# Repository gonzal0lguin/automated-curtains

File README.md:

# automated-curtains

Motorized roller blinds controlled by an ESP32: a NEMA 17 stepper with a
TMC2209 driver, an AS5600 magnetic encoder for absolute position, and a
smart-knob style controller (rotary encoder and GC9A01 round display). It also
has a web app and API, so an iPhone Shortcut can open the blinds when the alarm
goes off.

- Project idea and goals: [idea.md](idea.md)
- Firmware, wiring, setup, API and testing: [firmware/README.md](firmware/README.md)

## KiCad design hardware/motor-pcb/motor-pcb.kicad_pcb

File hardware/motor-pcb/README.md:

# Smart Blinds — motor encoder board

KiCad 10 project for the small board that sits on the back of the NEMA 17
stepper. It carries the AS5600 magnetic encoder on the shaft axis and the
RJ45 that links the motor to the control panel
([`../blinds-pcb`](../blinds-pcb/README.md)).

**Status: rev A, first layout** (2026-11-17). Schematic ERC clean
([`doc/schematic.pdf`](doc/schematic.pdf)); PCB placed, routed, DRC clean
(0 violations, 0 unconnected, schematic parity clean); fabrication files in
[`fab/`](fab/).

| Outer face | Motor side |
|---|---|
|  |  |

(The motor-side render is seen from below, so it is mirrored.)

## What is on the board

| Ref | Part | Side | Why |
|---|---|---|---|
| U1 | AS5600-ASOM, SOIC-8 | motor | 12-bit angle of the magnet on the shaft, I2C address 0x36 |
| C1, C2 | 100 nF + 1 µF | motor | AS5600 supply (3.3 V operation: VDD5V and VDD3V3 tied together, as in the datasheet) |
| JP1 | 3-pad solder jumper | motor | AS5600 DIR pin. Default bridged to GND (CW); cut and bridge 2–3 for CCW |
| J1 | RJ45 Amphenol 54602-908LF, no magnetics | outer | Cable to the panel. Same jack and pinout as panel J2 |
| J2 | JST-XH 4-pin, vertical | outer | Motor cable: 1 A1, 2 A2 (coil A), 3 B1, 4 B2 (coil B) |
| R1, R2 | 4.7k | outer | I2C pull-ups at the far end; with the panel's 10k ≈ 3.2k total |
| D2 | PESD3V3L2BT | outer | ESD clamp on SDA / SCL where the cable enters |
| C3 | 10 µF | outer | 3V3 bulk at the cable entry |
| R3, D1 | 1k + green LED | outer | Lights when the cable brings 3V3 (≈1 mA) |
| TP1–TP3 | test pads | outer | 3V3, GND, AS5600 OUT (analog angle). SDA / SCL: probe R1 / R2 |
| H1–H4 | M3, non-plated | — | 31 mm NEMA 17 hole pattern |

RJ45 pinout (straight T568B cable, identical to the panel):

| Pin | 1 | 2 | 3 | 4 | 5 | 6 | 7 | 8 |
|---|---|---|---|---|---|---|---|---|
| Signal | Coil A1 | Coil A2 | Coil B1 | SDA | GND | Coil B2 | SCL | 3V3 |

**Not Ethernet.** Never plug it into a network device, and never unplug it
while the panel is powered (motor coils).

## Mechanics

- Board 42.3 × 42.3 mm (the motor body), corners r 3, 1.6 mm FR-4.
- Mounted with four long M3 screws through the motor's own holes (31 mm
  pattern) and spacers. Copper is kept 3.6 mm from each hole for washers
  and spacers; the holes are not plated and not connected to GND (the motor
  case stays floating).
- U1 is exactly on the board centre = shaft axis, on the side facing the
  motor. Needs a **dual-shaft motor** (or a magnet holder on the rear shaft).
- Magnet: diametrically magnetised, Ø6 × 2.5 mm (Ø8 × 3 also works), glued
  centred on the shaft end. Air gap magnet face → chip top **0.5–3 mm**
  (chip is 1.5 mm tall). Choose the spacer length for this.
- Only U1, C1, C2, JP1 are on the motor side. **Trim the RJ45 and XH leads
  flush** after soldering (they come through on the motor side).
- Coil tracks are 0.8 mm (0.6 mm for B2), routed as pairs along the left and
  bottom edges, at least 7 mm from U1. At 1 A they make well under 1 mT at
  the chip, against the magnet's 30–90 mT, and the AS5600 rejects uniform
  stray fields.

## Firmware notes

- Same bus as before: AS5600 at 0x36 on GPIO21/22; keep `I2C_FREQ_HZ 100000`
  (see `../blinds-pcb/doc/pinmap.md`).
- JP1 default (DIR = GND): the angle rises clockwise **seen from the chip
  top**, i.e. from the motor towards the board. If the closed loop counts the
  wrong way, flip it in firmware or re-bridge JP1 — do not swap coil wires.
- AS5600 OUT on TP3 gives an analog angle (0–3.3 V) for a quick magnet check
  with a multimeter while turning the shaft by hand.

## Ordering

`fab/motor-pcb-gerbers.zip` (gerbers + drills), `fab/motor-pcb-pos.csv`,
`fab/lcsc-order.csv`. 2 layers, 1.6 mm, any colour; JLCPCB minimums are met
(0.25 mm tracks, 0.3 mm vias, 0.15 mm silk lines, 0.8 mm text).

**AS5600 stock:** LCSC C79815 showed only 7 pieces on 2026-11-17; buy it at
Mouser / Digi-Key if needed. Do **not** substitute the AS5600L: same package,
but I2C address 0x40 (the firmware expects 0x36).

## Files and scripts

| File | Contents |
|---|---|
| `tools/gen_schematic.py` | Writes `motor-pcb.kicad_sch` and checks the netlist (uses `../blinds-pcb/tools/gen_schematic/sch.py`) |
| `tools/build_pcb.py` | Rebuilds the whole board from the schematic: footprints, outline, holes, placement, routing, GND zones |
| `tools/silk.py` | Silkscreen: references, labels, flag, emblem |
| `tools/artwork.py` | Flag drawing and emblem helpers, shared by `silk.py` and `export_svg.py` (no KiCad needed) |
| `tools/export_svg.py` | Writes the logos as SVG to [`../artwork/`](../artwork/README.md) (with and without text / hatching) |
| `tools/emblem_small.py` | Small "ANDES MADE" volcano emblem (reuses the panel's `emblem.py`), writes `tools/emblem_small.json` |
| `lib/motor.kicad_sym` | AS5600 symbol (KiCad has none) |

Script order, KiCad closed: `gen_schematic.py` → `build_pcb.py` → `silk.py`,
then DRC. **Every script overwrites its output**, including edits made by hand
in KiCad; once the board is edited by hand, stop re-running them.

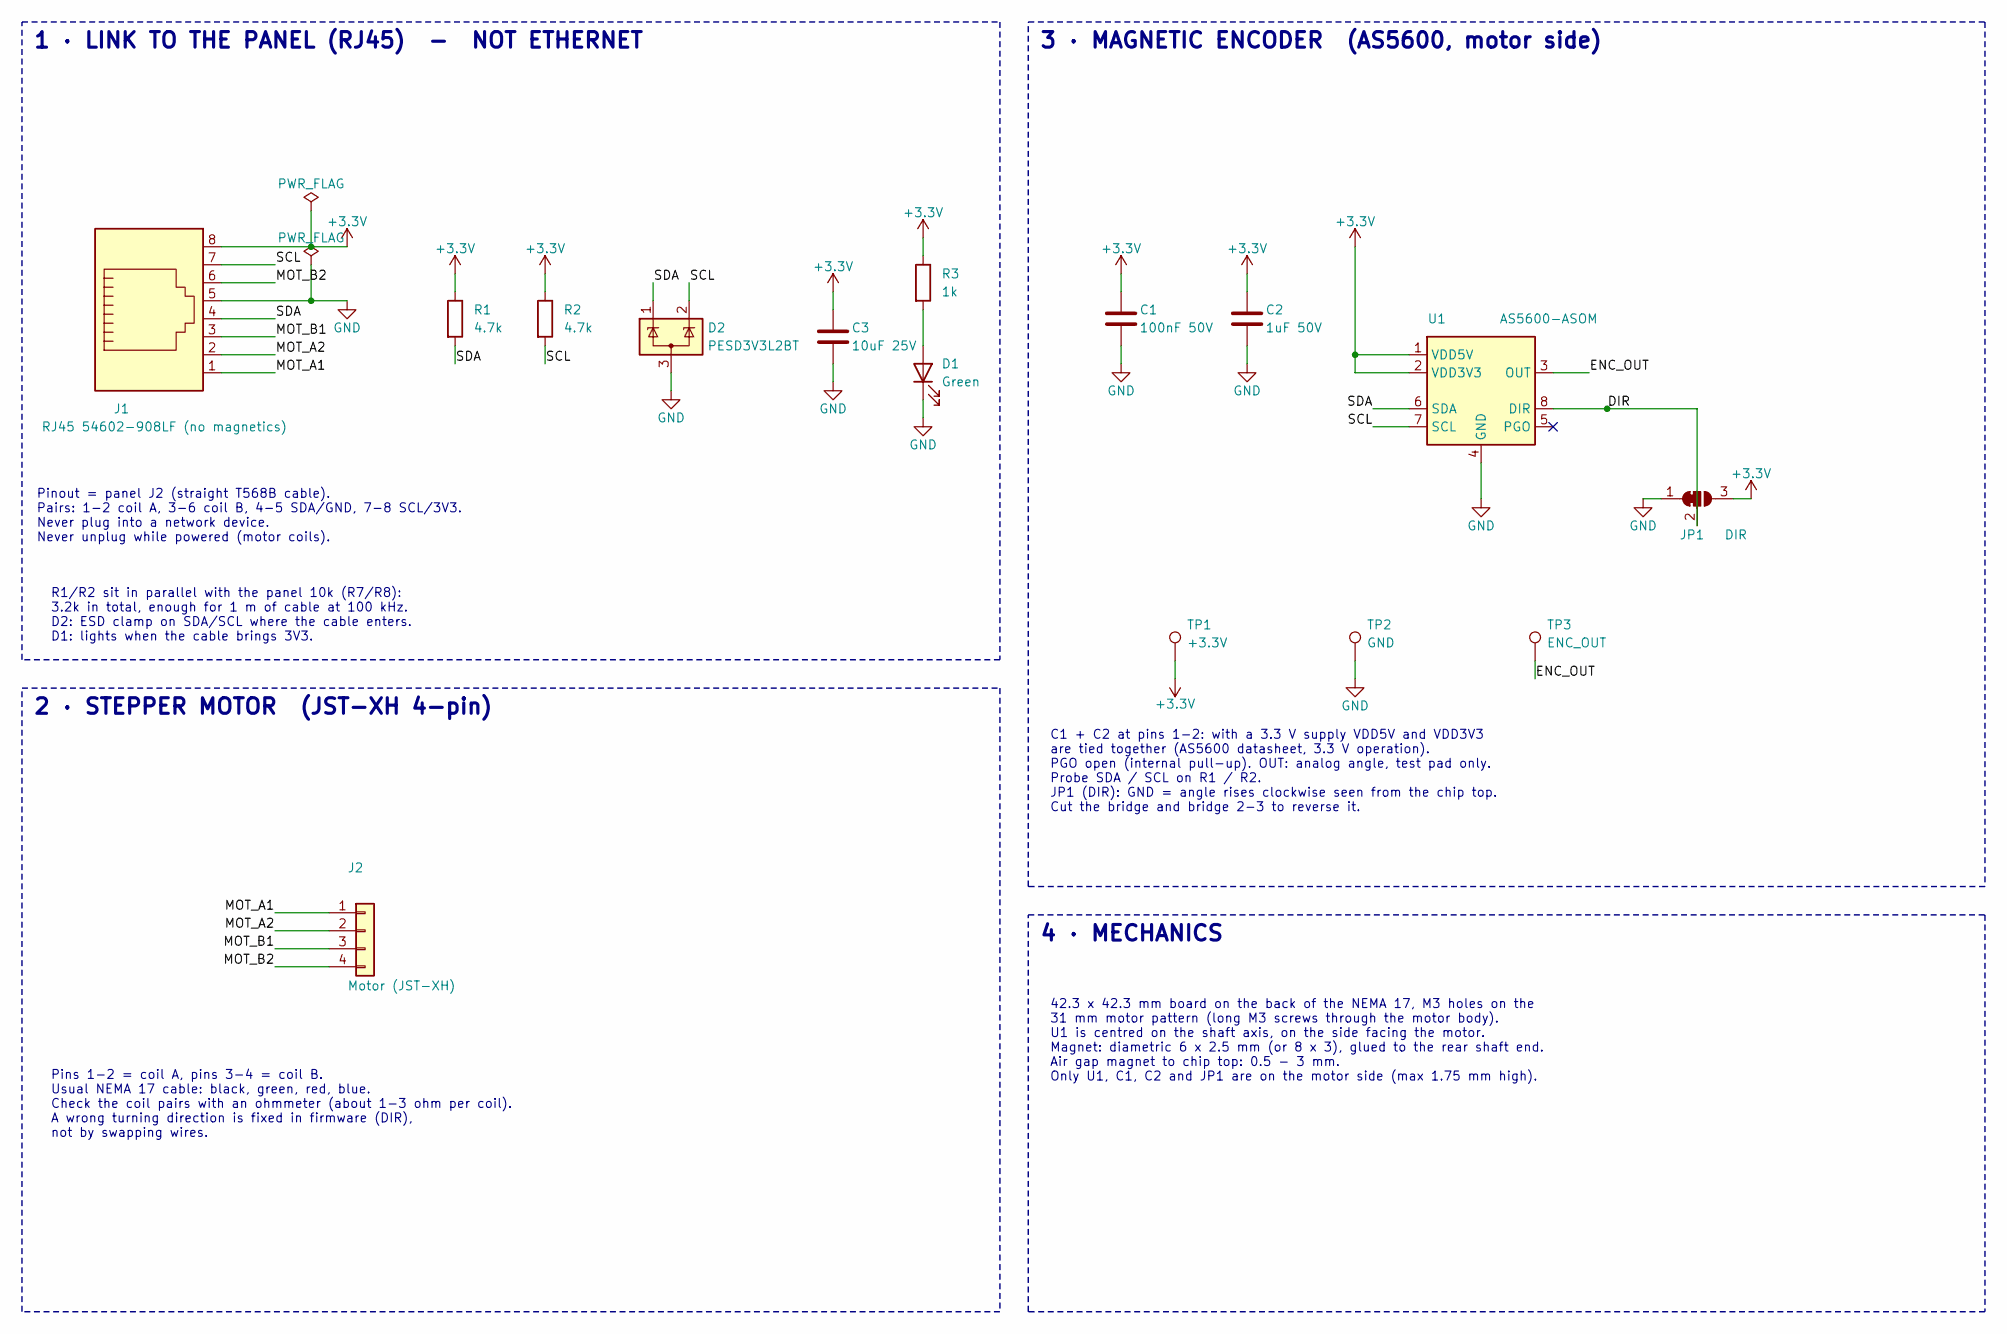
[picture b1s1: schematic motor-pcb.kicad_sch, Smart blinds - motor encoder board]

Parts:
C1: 100nF 50V; C_0805_2012Metric_Pad1.18x1.45mm_HandSolder; LCSC C38141
C2: 1uF 50V; C_0805_2012Metric_Pad1.18x1.45mm_HandSolder; LCSC C28323
C3: 10uF 25V; C_0805_2012Metric_Pad1.18x1.45mm_HandSolder; LCSC C92009
D1: Green; LED_0805_2012Metric_Pad1.15x1.40mm_HandSolder; LCSC C2297
D2: PESD3V3L2BT; SOT-23; LCSC C55440
J1: RJ45 54602-908LF (no magnetics); RJ45_Amphenol_54602-x08_Horizontal; LCSC C2847314
J2: Motor (JST-XH); JST_XH_B4B-XH-A_1x04_P2.50mm_Vertical; LCSC C144395
JP1: DIR; SolderJumper-3_P1.3mm_Bridged12_RoundedPad1.0x1.5mm
R1, R2: 4.7k; R_0805_2012Metric_Pad1.20x1.40mm_HandSolder; LCSC C17673
R3: 1k; R_0805_2012Metric_Pad1.20x1.40mm_HandSolder
TP1: +3.3V; TestPoint_Pad_D1.5mm
TP2: GND; TestPoint_Pad_D1.5mm
TP3: ENC_OUT; TestPoint_Pad_D1.5mm
U1: AS5600-ASOM; SOIC-8_3.9x4.9mm_P1.27mm; LCSC C79815

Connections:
+3.3V: C1.1, C2.1, C3.1, J1.8, JP1.3 (B), R1.1, R2.1, R3.1, TP1.1, U1.1 (VDD5V), U1.2 (VDD3V3)
/DIR: JP1.2 (C), U1.8 (DIR)
/ENC_OUT: TP3.1, U1.3 (OUT)
/MOT_A1: J1.1, J2.1
/MOT_A2: J1.2, J2.2
/MOT_B1: J1.3, J2.3
/MOT_B2: J1.6, J2.4
/SCL: D2.2 (K), J1.7, R2.2, U1.7 (SCL)
/SDA: D2.1 (K), J1.4, R1.2, U1.6 (SDA)
GND: C1.2, C2.2, C3.2, D1.1 (K), D2.3 (A), J1.5, JP1.1 (A), TP2.1, U1.4 (GND)
unnamed: D1.2 (A), R3.2

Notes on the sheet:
1 · LINK TO THE PANEL (RJ45) - NOT ETHERNET
Pinout = panel J2 (straight T568B cable). Pairs: 1-2 coil A, 3-6 coil B, 4-5 SDA/GND, 7-8 SCL/3V3. Never plug into a network device. Never unplug while powered (motor coils).
R1/R2 sit in parallel with the panel 10k (R7/R8): 3.2k in total, enough for 1 m of cable at 100 kHz. D2: ESD clamp on SDA/SCL where the cable enters. D1: lights when the cable brings 3V3.
2 · STEPPER MOTOR (JST-XH 4-pin)
Pins 1-2 = coil A, pins 3-4 = coil B. Usual NEMA 17 cable: black, green, red, blue. Check the coil pairs with an ohmmeter (about 1-3 ohm per coil). A wrong turning direction is fixed in firmware (DIR), not by swapping wires.
3 · MAGNETIC ENCODER (AS5600, motor side)
C1 + C2 at pins 1-2: with a 3.3 V supply VDD5V and VDD3V3 are tied together (AS5600 datasheet, 3.3 V operation). PGO open (internal pull-up). OUT: analog angle, test pad only. Probe SDA / SCL on R1 / R2. JP1 (DIR): GND = angle rises clockwise seen from the chip top. Cut the bridge and bridge 2-3 to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
4 · MECHANICS
42.3 x 42.3 mm board on the back of the NEMA 17, M3 holes on the 31 mm motor pattern (long M3 screws through the motor body). U1 is centred on the shaft axis, on the side facing the motor. Magnet: diametric 6 x 2.5 mm (or 8 x 3), glued to the rear shaft end. Air gap magnet to chip top: 0.5 - 3 mm. 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

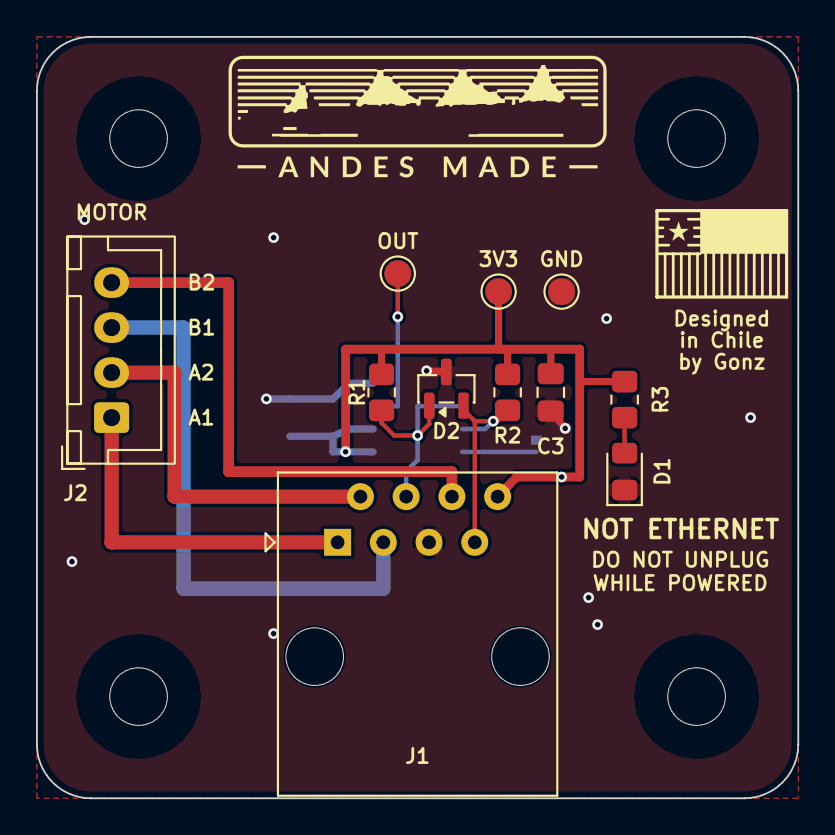
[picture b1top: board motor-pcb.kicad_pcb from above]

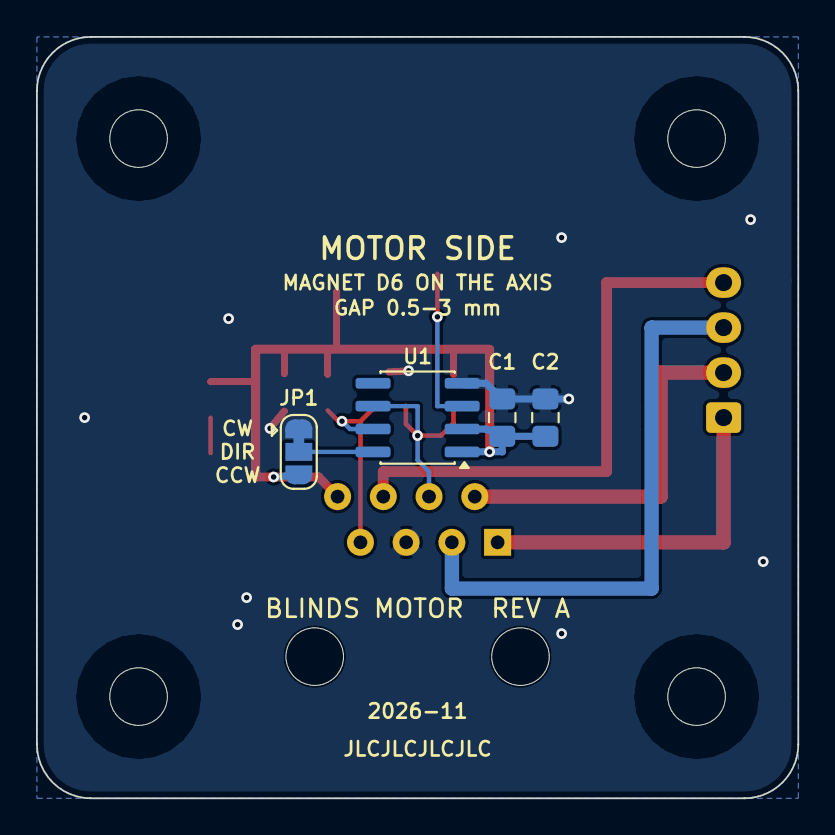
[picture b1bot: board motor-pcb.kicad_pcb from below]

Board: 2 copper layers, 42.3 x 42.3 mm, 19 parts (4 on the bottom side), 11 nets.

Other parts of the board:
H1, H2, H3, H4: M3; MountingHole_3.2mm_M3

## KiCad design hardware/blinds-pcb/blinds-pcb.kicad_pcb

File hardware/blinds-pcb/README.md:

# Smart Blinds — control panel PCB

KiCad 10 project for the wall control panel of the motorized blind: a round
board that carries the ESP32, the stepper driver, the ring knob, the LED ring
and the connectors for the round display and the motor.

**Status: rev A ready to order** (2026-11-15). Schematic ERC clean
([`doc/schematic.pdf`](doc/schematic.pdf)); PCB placed, routed and DRC clean;
fabrication files and the order guide are in [`fab/`](fab/README.md).

## What is on the board

| Block | Part |
|---|---|
| Controller | ESP32 NodeMCU 38-pin, in sockets |
| Motor driver | BigTreeTech TMC2209 module, in sockets |
| Knob | ALPS EC35A1520402 ring encoder + centre tact switch |
| Lights | 10 × WS2812B with a 5 V level shifter |
| Power | 12 V barrel jack, fuse, reverse-polarity and surge protection, 5 V 2 A buck (AP63205) |
| Display | Connector for a GC9A01 1.28" round LCD module |
| Motor link | RJ45 to the NEMA 17 and its AS5600 encoder (**not Ethernet**) |
| Extras | Ambient light sensor, 12 V sense, RESET/BOOT buttons, spare I2C header |

## Documents

| File | Contents |
|---|---|
| [`doc/hardware-design.md`](doc/hardware-design.md) | Every circuit block explained: what it does, why each value, what to check |
| [`doc/pinmap.md`](doc/pinmap.md) | ESP32 pin map, connector pinouts, firmware edits for the PCB |
| [`doc/bom.md`](doc/bom.md) | Parts list with packages and LCSC numbers |
| [`doc/schematic.pdf`](doc/schematic.pdf) | Printable schematic |
| [`doc/pcb-layout.md`](doc/pcb-layout.md) | Placement, routing, keep-outs, silkscreen, DRC state |
| [`fab/README.md`](fab/README.md) | Gerbers, LCSC order list, how to order, checks before paying |
| [`doc/PLAN.md`](doc/PLAN.md) | Working plan, decisions and log |
| [`tools/gen_schematic/`](tools/gen_schematic/) | Script that generated the schematic and checks its netlist. **Re-running it overwrites edits made in KiCad** |
| `tools/pcb_placement/`, `tools/pcb_routing/`, `tools/pcb_silk/` | Placement, routing and silkscreen scripts. The board now has hand edits and review fixes: **do not re-run `place.py` or `route.py`** (see `doc/pcb-layout.md`) |
| [`doc/Curtain control panel hardware design.pdf`](doc/Curtain%20control%20panel%20hardware%20design.pdf) | Earlier design study, including the press-the-screen mechanism |
| [`../motor-pcb/README.md`](../motor-pcb/README.md) | Motor encoder board (AS5600 + RJ45 on the back of the NEMA 17) |
| [`../../firmware/README.md`](../../firmware/README.md) | Firmware: build, flash, test firmwares, API |

## Opening the project

Open `blinds-pcb.kicad_pro` with KiCad 10 or newer. Project-specific symbols,
footprints and 3D models are in `lib/` (`blinds.kicad_sym`, `blinds.pretty/`,
`3d/`) and are found through `${KIPRJMOD}`, so no global library setup is needed.

## Things to know before powering it

- **Supply:** 12 V DC, 2 A, centre-positive, 5.5 mm barrel plug.
- **The RJ45 port carries 12 V motor current.** Never connect it to a
  computer, router or switch, and never unplug it while the board is powered.
- **Motor current** is set by the firmware over UART; keep it at or below
  about 1 A RMS because it flows through the RJ45 cable.
- **USB and 12 V together are fine:** a diode stops USB from powering the
  LED ring or back-feeding the regulator. The NodeMCU itself has no diode on
  its USB 5 V, so do not leave it plugged into a computer that is switched
  off while the 12 V adapter is on.
- **Flashing:** plug USB into the NodeMCU while it sits in the board. If
  automatic download mode fails, hold BOOT, tap RESET, release BOOT.
- **Firmware pins differ from the breadboard prototype.** Apply the edits
  listed in [`doc/pinmap.md`](doc/pinmap.md) before flashing a PCB build.

Assembly order and the bring-up checklist are at the end of
[`doc/hardware-design.md`](doc/hardware-design.md).

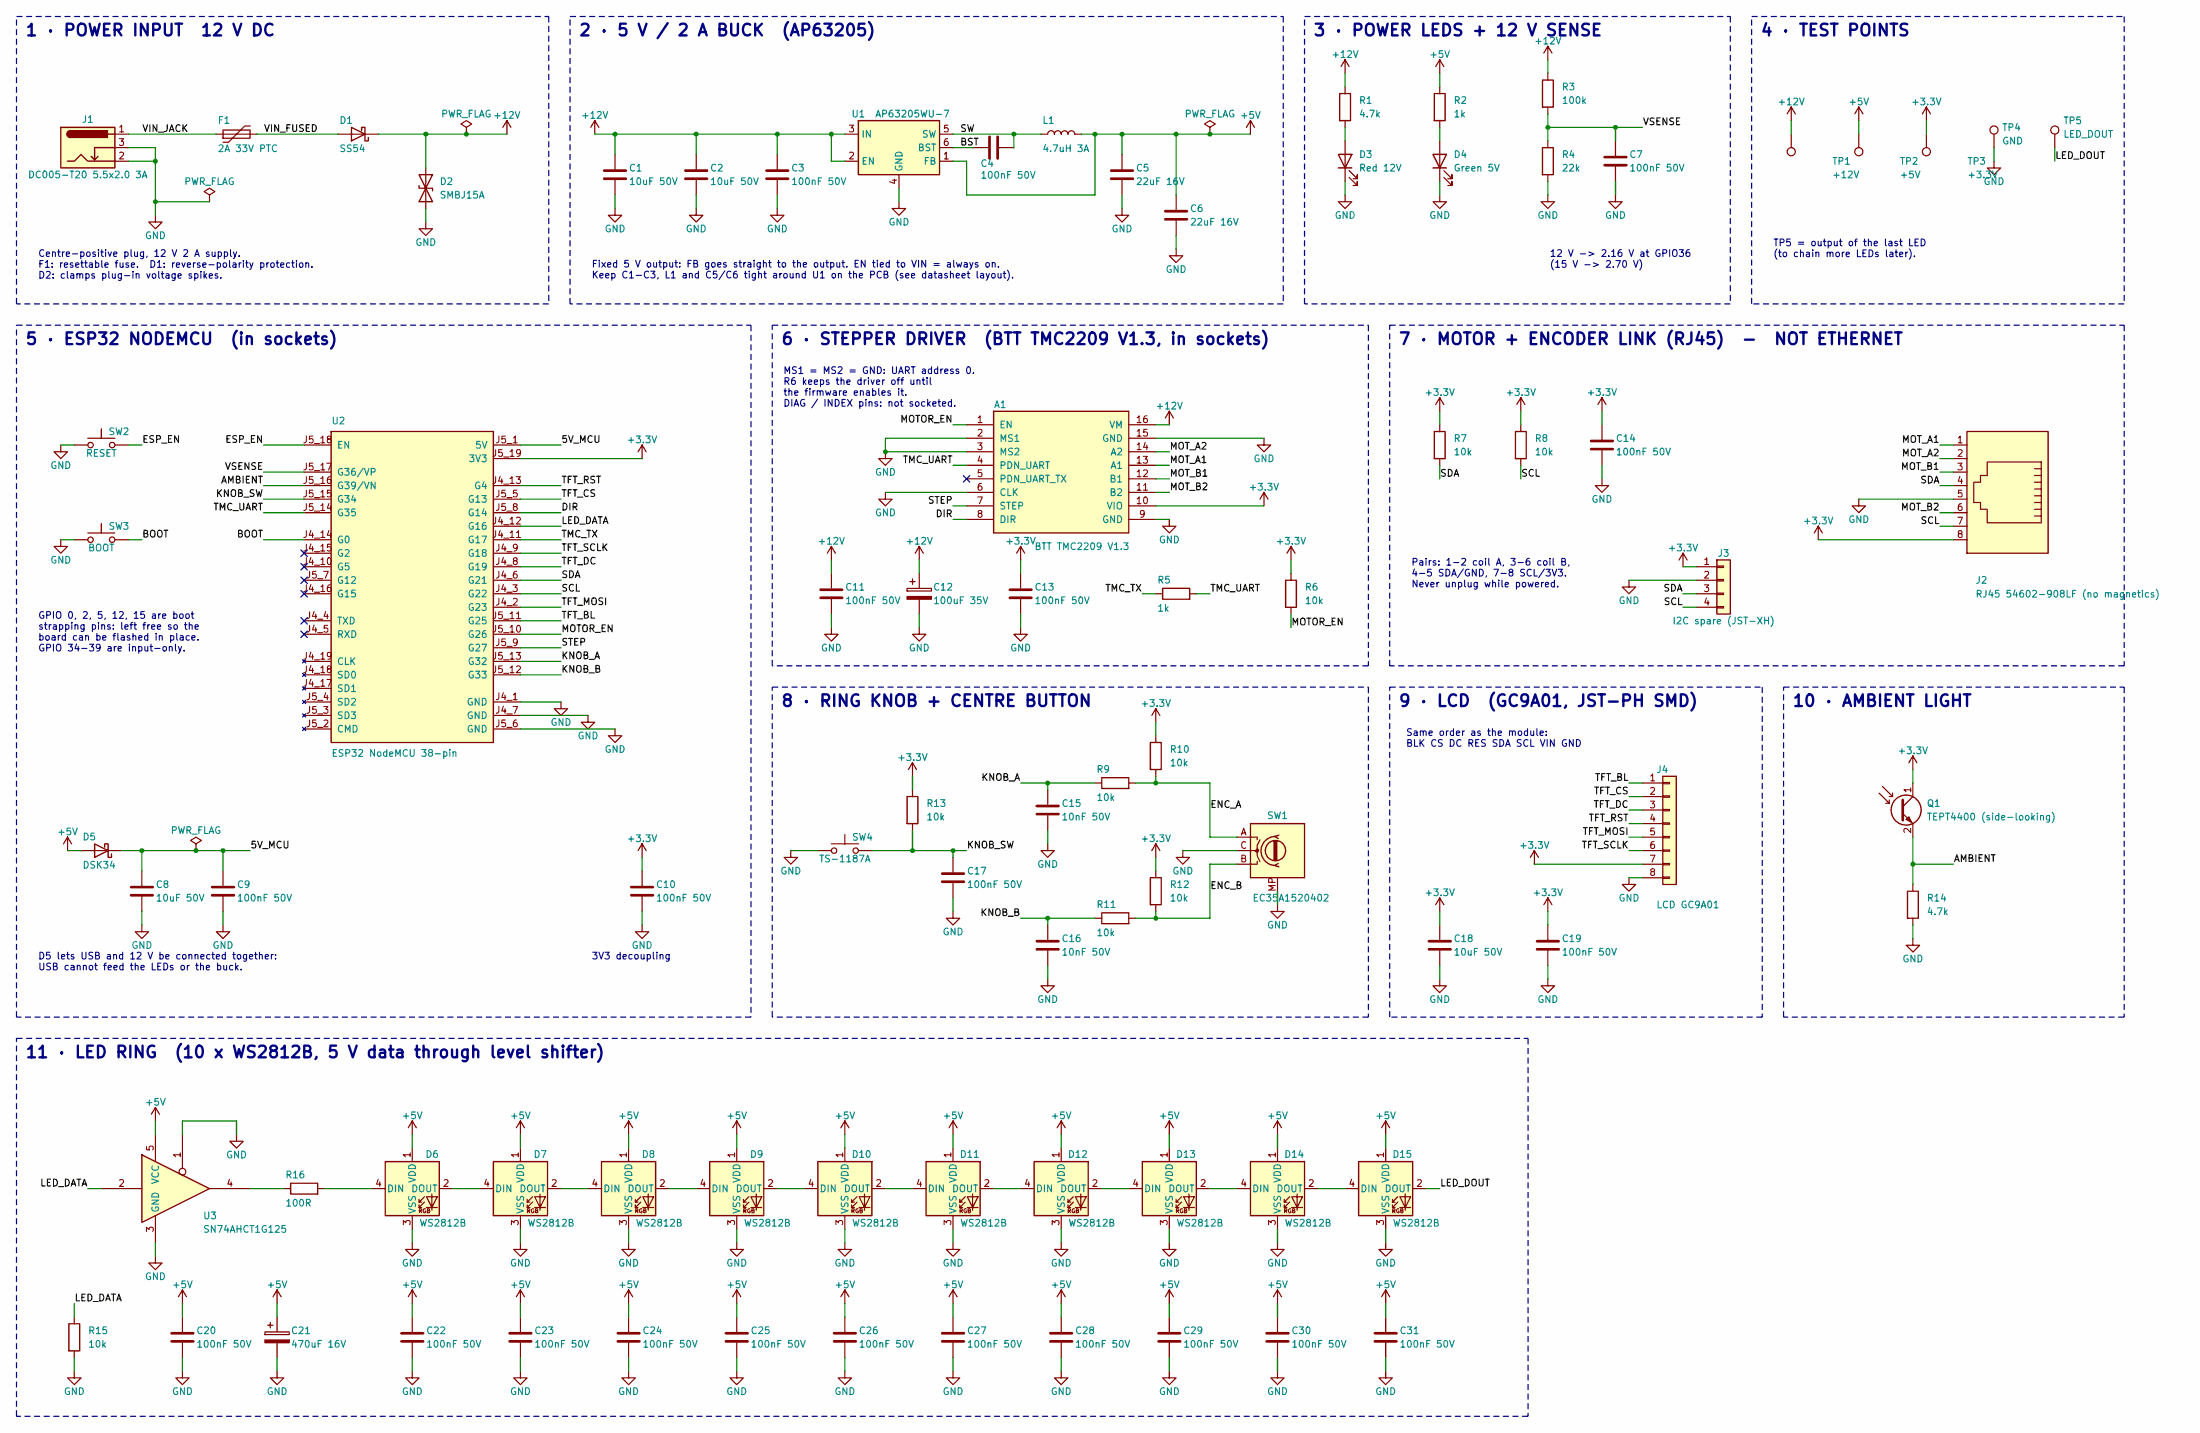
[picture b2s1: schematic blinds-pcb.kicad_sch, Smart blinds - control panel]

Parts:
A1: BTT TMC2209 V1.3; Pololu_Breakout-16_15.2x20.3mm
C1, C2, C8, C18: 10uF 50V; C_1206_3216Metric_Pad1.33x1.80mm_HandSolder; LCSC C13585
C3, C4, C7, C9, C10, C11, C13, C14, C17, C19, C20, C22, C23, C24, C25, C26, C27, C28, C29, C30, C31: 100nF 50V; C_0805_2012Metric_Pad1.18x1.45mm_HandSolder; LCSC C38141
C5, C6: 22uF 16V; C_0805_2012Metric_Pad1.18x1.45mm_HandSolder; LCSC C98190
C12: 100uF 35V; CP_Radial_D6.3mm_P2.50mm; LCSC C109392
C15, C16: 10nF 50V; C_0805_2012Metric_Pad1.18x1.45mm_HandSolder; LCSC C1710
C21: 470uF 16V; CP_Radial_D8.0mm_P3.50mm; LCSC C2943989
D1: SS54; D_SMA_Handsoldering; LCSC C7420369
D2: SMBJ15A; D_SMB_Handsoldering; LCSC C726824
D3: Red 12V; LED_0805_2012Metric_Pad1.15x1.40mm_HandSolder; LCSC C2295
D4: Green 5V; LED_0805_2012Metric_Pad1.15x1.40mm_HandSolder; LCSC C2297
D5: DSK34; D_SOD-123; LCSC C727076
D6, D7, D8, D9, D10, D11, D12, D13, D14, D15: WS2812B; LED_WS2812B_PLCC4_5.0x5.0mm_P3.2mm; LCSC C114588
F1: 2A 33V PTC; Fuse_1812_4532Metric_Pad1.30x3.40mm_HandSolder; LCSC C18198343
J1: DC005-T20 5.5x2.0 3A; BarrelJack_Horizontal; LCSC C111567
J2: RJ45 54602-908LF (no magnetics); RJ45_Amphenol_54602-x08_Horizontal; LCSC C2847314
J3: I2C spare (JST-XH); JST_XH_B4B-XH-A_1x04_P2.50mm_Vertical; LCSC C594232
J4: LCD GC9A01; JST_PH_S8B-PH-SM4-TB_1x08-1MP_P2.00mm_Horizontal; LCSC C265121
L1: 4.7uH 3A; L_Changjiang_FNR6045S; LCSC C168067
Q1: TEPT4400 (side-looking); LED_D3.0mm_Horizontal_O1.27mm_Z2.0mm_Clear; LCSC C132178
R1, R14: 4.7k; R_0805_2012Metric_Pad1.20x1.40mm_HandSolder; LCSC C17673
R2, R5: 1k; R_0805_2012Metric_Pad1.20x1.40mm_HandSolder; LCSC C17513
R3: 100k; R_0805_2012Metric_Pad1.20x1.40mm_HandSolder; LCSC C149504
R4: 22k; R_0805_2012Metric_Pad1.20x1.40mm_HandSolder; LCSC C17560
R6, R7, R8, R9, R10, R11, R12, R13, R15: 10k; R_0805_2012Metric_Pad1.20x1.40mm_HandSolder; LCSC C17414
R16: 100R; R_0805_2012Metric_Pad1.20x1.40mm_HandSolder; LCSC C17408
SW1: EC35A1520402; RotaryEncoder_Alps_EC35A1520402
SW2: RESET; SW_Tactile_SPST_Angled_PTS645Vx31-2LFS; LCSC C285519
SW3: BOOT; SW_Tactile_SPST_Angled_PTS645Vx31-2LFS; LCSC C285519
SW4: TS-1187A; SW_Push_1P1T_XKB_TS-1187A; LCSC C318889
TP1: +12V; TestPoint_Pad_D1.5mm
TP2: +5V; TestPoint_Pad_D1.5mm
TP3: +3.3V; TestPoint_Pad_D1.5mm
TP4: GND; TestPoint_Pad_D1.5mm
TP5: LED_DOUT; TestPoint_Pad_D1.5mm
U1: AP63205WU-7; TSOT-23-6_HandSoldering; LCSC C2071056
U2: ESP32 NodeMCU 38-pin; ESP32_NODEMCU
U3: SN74AHCT1G125; SOT-23-5_HandSoldering; LCSC C7484

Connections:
+3.3V: A1.10 (VIO), C10.1, C13.1, C14.1, C18.1, C19.1, J2.8, J3.1, J4.7, Q1.1 (C), R6.1, R7.1, R8.1, R10.1, R12.1, R13.1, TP3.1 (1_1), U2.J5_19 (3V3)
+5V: C5.1, C6.1, C20.1, C21.1, C22.1, C23.1, C24.1, C25.1, C26.1, C27.1, C28.1, C29.1, C30.1, C31.1, D5.2 (A), D6.1 (VDD), D7.1 (VDD), D8.1 (VDD), D9.1 (VDD), D10.1 (VDD), D11.1 (VDD), D12.1 (VDD), D13.1 (VDD), D14.1 (VDD), D15.1 (VDD), L1.2, R2.1, TP2.1 (1_1), U1.1 (FB), U3.5 (VCC)
+12V: A1.16 (VM), C1.1, C2.1, C3.1, C11.1, C12.1, D1.1 (K), D2.1 (A1), R1.1, R3.1, TP1.1 (1_1), U1.2 (EN), U1.3 (IN)
/5V_MCU: C8.1, C9.1, D5.1 (K), U2.J5_1 (5V)
/AMBIENT: Q1.2 (E), R14.1, U2.J5_16 (G39/VN)
/BOOT: SW3.2, U2.J4_14 (G0)
/BST: C4.1, U1.6 (BST)
/DIR: A1.8 (DIR), U2.J5_8 (G14)
/ENC_A: R9.2, R10.2, SW1.A
/ENC_B: R11.2, R12.2, SW1.B
/ESP_EN: SW2.2, U2.J5_18 (EN)
/KNOB_A: C15.1, R9.1, U2.J5_13 (G32)
/KNOB_B: C16.1, R11.1, U2.J5_12 (G33)
/KNOB_SW: C17.1, R13.2, SW4.2, U2.J5_15 (G34)
/LED_DATA: R15.1, U2.J4_12 (G16), U3.2
/LED_DOUT: D15.2 (DOUT), TP5.1 (1_1)
/MOTOR_EN: A1.1 (EN), R6.2, U2.J5_10 (G26)
/MOT_A1: A1.13 (A1), J2.1
/MOT_A2: A1.14 (A2), J2.2
/MOT_B1: A1.12 (B1), J2.3
/MOT_B2: A1.11 (B2), J2.6
/SCL: J2.7, J3.4, R8.2, U2.J4_3 (G22)
/SDA: J2.4, J3.3, R7.2, U2.J4_6 (G21)
/STEP: A1.7 (STEP), U2.J5_9 (G27)
/SW: C4.2, L1.1, U1.5 (SW)
/TFT_BL: J4.1, U2.J5_11 (G25)
/TFT_CS: J4.2, U2.J5_5 (G13)
/TFT_DC: J4.3, U2.J4_8 (G19)
/TFT_MOSI: J4.5, U2.J4_2 (G23)
/TFT_RST: J4.4, U2.J4_13 (G4)
/TFT_SCLK: J4.6, U2.J4_9 (G18)
/TMC_TX: R5.1, U2.J4_11 (G17)
/TMC_UART: A1.4 (PDN_UART), R5.2, U2.J5_14 (G35)
/VIN_FUSED: D1.2 (A), F1.2
/VIN_JACK: F1.1, J1.1
/VSENSE: C7.1, R3.2, R4.1, U2.J5_17 (G36/VP)
GND: A1.2 (MS1), A1.3 (MS2), A1.6 (CLK), A1.9 (GND), A1.15 (GND), C1.2, C2.2, C3.2, C5.2, C6.2, C7.2, C8.2, C9.2, C10.2, C11.2, C12.2, C13.2, C14.2, C15.2, C16.2, C17.2, C18.2, C19.2, C20.2, C21.2, C22.2, C23.2, C24.2, C25.2, C26.2, C27.2, C28.2, C29.2, C30.2, C31.2, D2.2 (A2), D3.1 (K), D4.1 (K), D6.3 (VSS), D7.3 (VSS), D8.3 (VSS), D9.3 (VSS), D10.3 (VSS), D11.3 (VSS), D12.3 (VSS), D13.3 (VSS), D14.3 (VSS), D15.3 (VSS), J1.2, J1.3, J2.5, J3.2, J4.8, R4.2, R14.2, R15.2, SW1.C, SW1.MP, SW2.1, SW3.1, SW4.1, TP4.1 (1_1), U1.4 (GND), U2.J4_1 (GND), U2.J4_7 (GND), U2.J5_6 (GND), U3.1, U3.3 (GND)
unnamed: D3.2 (A), R1.2
unnamed: D4.2 (A), R2.2
unnamed: D6.4 (DIN), R16.2
unnamed: D6.2 (DOUT), D7.4 (DIN)
unnamed: D7.2 (DOUT), D8.4 (DIN)
unnamed: D8.2 (DOUT), D9.4 (DIN)
unnamed: D9.2 (DOUT), D10.4 (DIN)
unnamed: D10.2 (DOUT), D11.4 (DIN)
unnamed: D11.2 (DOUT), D12.4 (DIN)
unnamed: D12.2 (DOUT), D13.4 (DIN)
unnamed: D13.2 (DOUT), D14.4 (DIN)
unnamed: D14.2 (DOUT), D15.4 (DIN)
unnamed: R16.1, U3.4

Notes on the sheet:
8 · RING KNOB + CENTRE BUTTON
3 · POWER LEDS + 12 V SENSE
5 · ESP32 NODEMCU (in sockets)
7 · MOTOR + ENCODER LINK (RJ45) - NOT ETHERNET
3V3 decoupling
4 · TEST POINTS
Same order as the module: BLK CS DC RES SDA SCL VIN GND
D5 lets USB and 12 V be connected together: USB cannot feed the LEDs or the buck.
2 · 5 V / 2 A BUCK (AP63205)
TP5 = output of the last LED (to chain more LEDs later).
Fixed 5 V output: FB goes straight to the output. EN tied to VIN = always on. Keep C1-C3, L1 and C5/C6 tight around U1 on the PCB (see datasheet layout).
6 · STEPPER DRIVER (BTT TMC2209 V1.3, in sockets)
Centre-positive plug, 12 V 2 A supply. F1: resettable fuse. D1: reverse-polarity protection. D2: clamps plug-in voltage spikes.
Pairs: 1-2 coil A, 3-6 coil B, 4-5 SDA/GND, 7-8 SCL/3V3. Never unplug while powered.
1 · POWER INPUT 12 V DC
12 V -> 2.16 V at GPIO36 (15 V -> 2.70 V)
MS1 = MS2 = GND: UART address 0. R6 keeps the driver off until the firmware enables it. DIAG / INDEX pins: not socketed.
10 · AMBIENT LIGHT
11 · LED RING (10 x WS2812B, 5 V data through level shifter)
9 · LCD (GC9A01, JST-PH SMD)
GPIO 0, 2, 5, 12, 15 are boot strapping pins: left free so the board can be flashed in place. GPIO 34-39 are input-only.

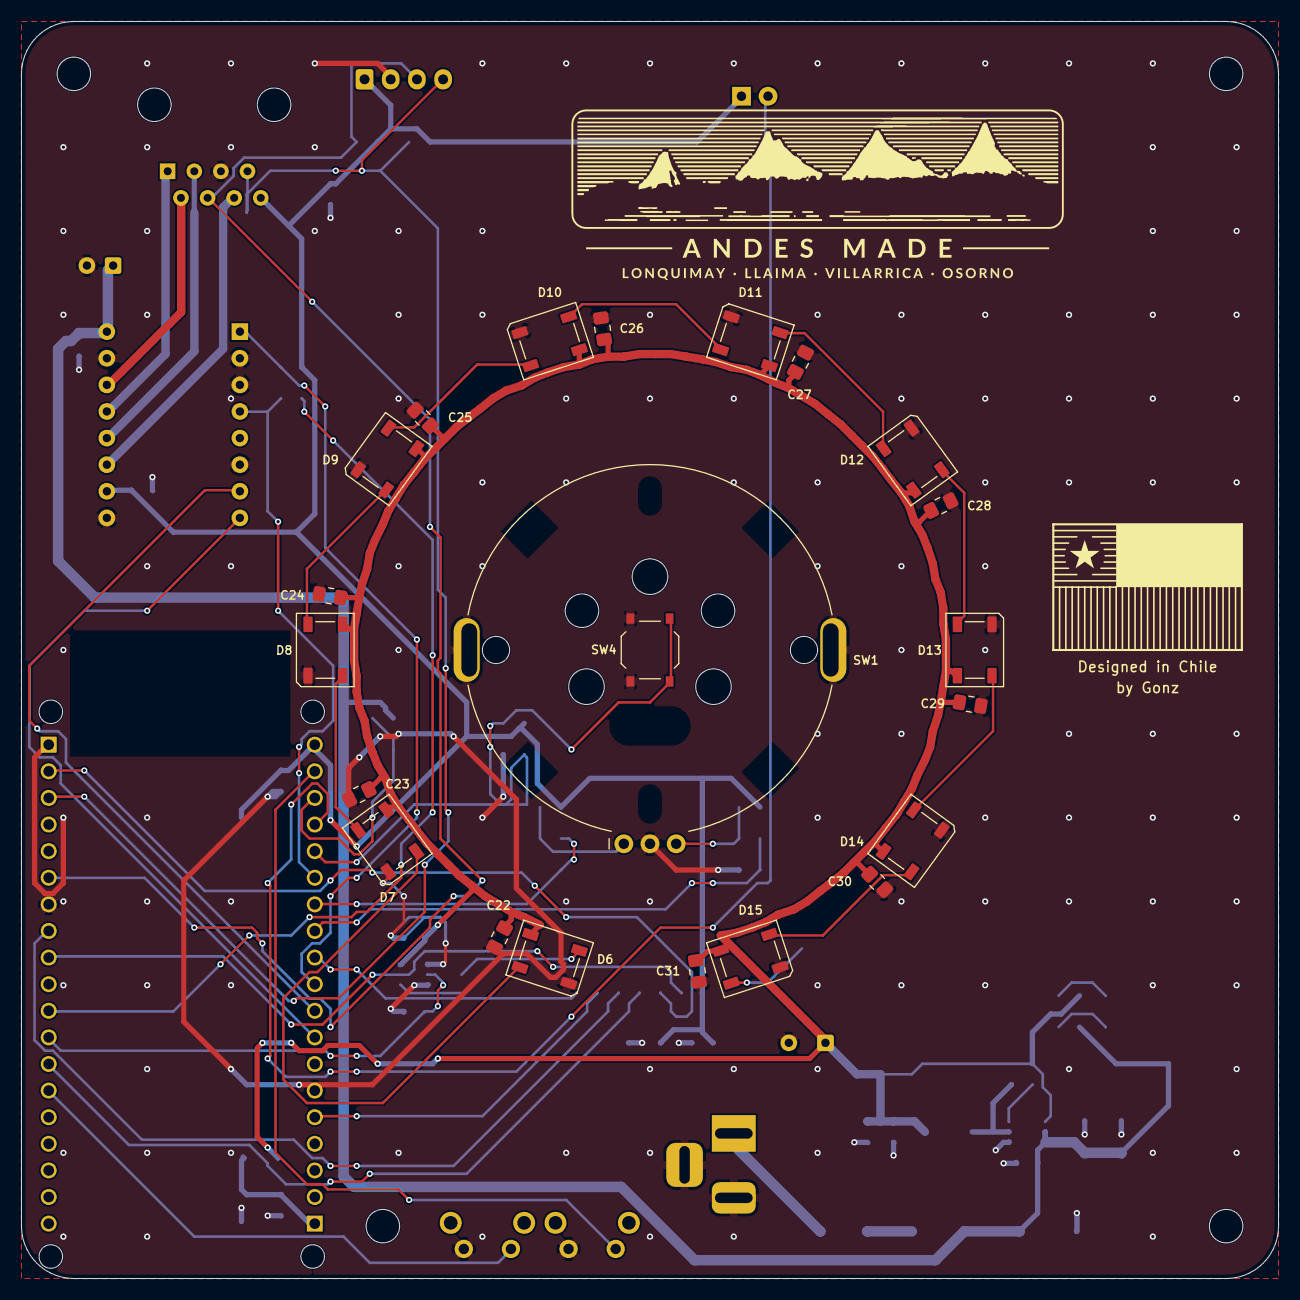
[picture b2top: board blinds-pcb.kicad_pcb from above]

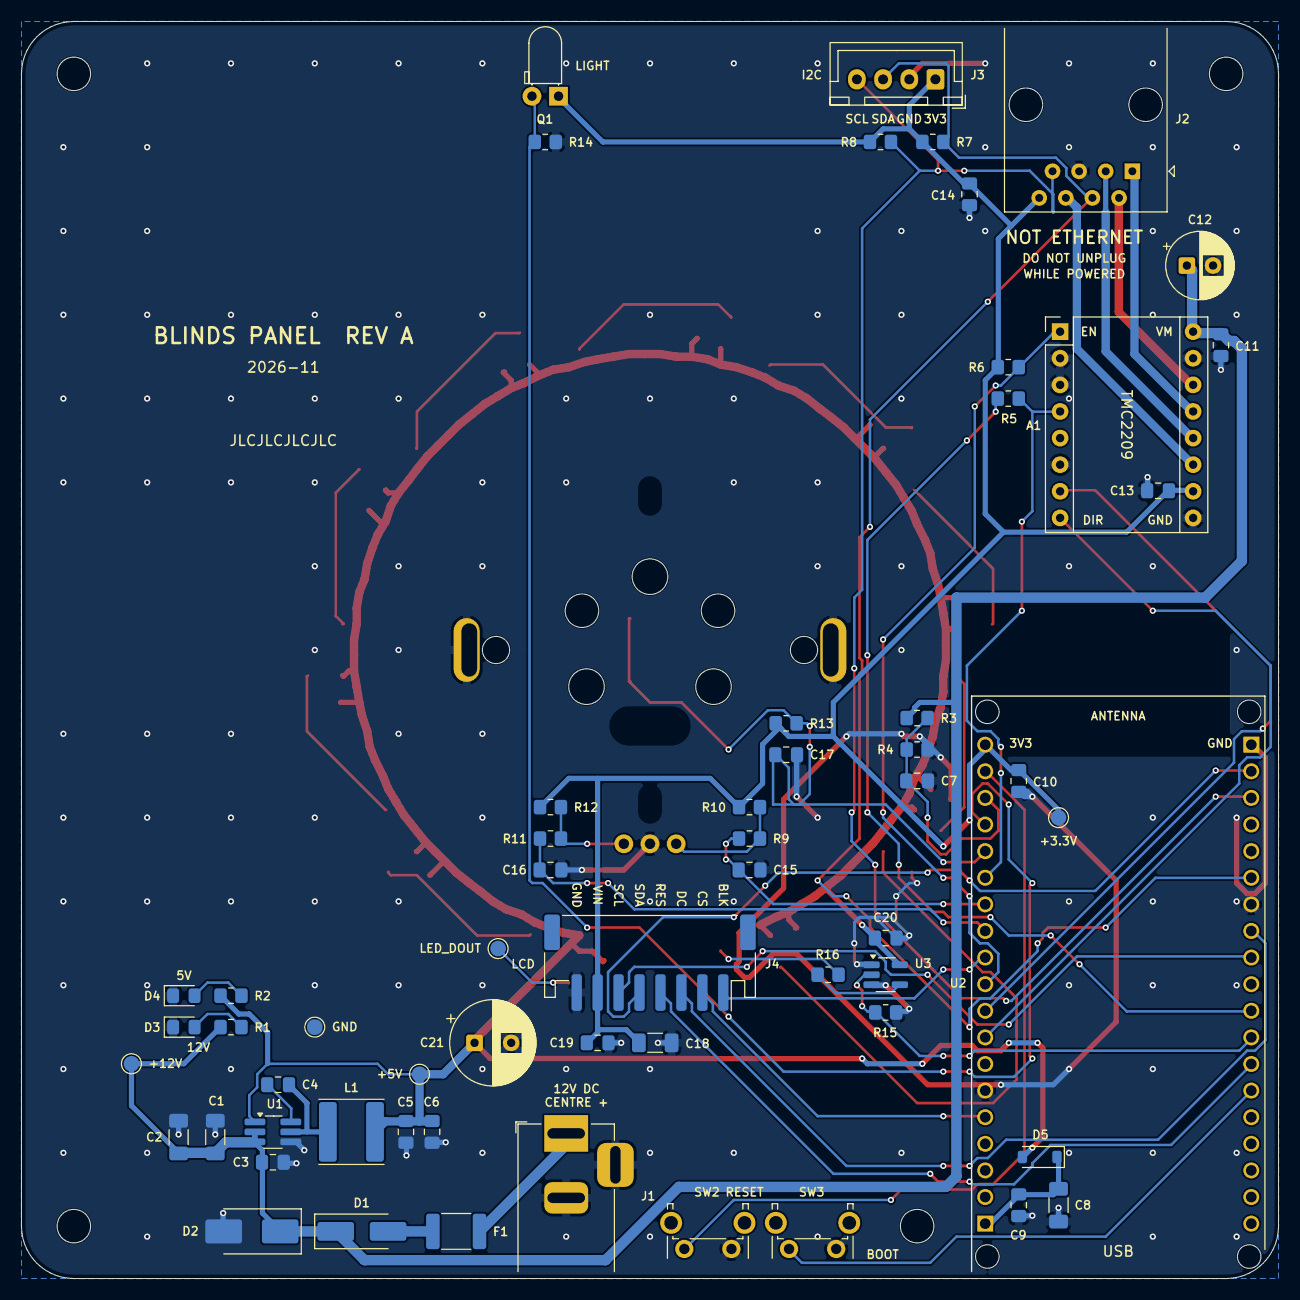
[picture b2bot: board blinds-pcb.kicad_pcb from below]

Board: 2 copper layers, 120.0 x 120.0 mm, 87 parts (60 on the bottom side), 50 nets.

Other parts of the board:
H1, H2, H3, H4: M3; MountingHole_3.2mm_M3
MECH1: Knob_Centre_Mechanics

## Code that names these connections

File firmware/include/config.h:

#pragma once
// =============================================================================
//  Hardware configuration — single source of truth for pins and constants.
//  Runtime-tunable values (speeds, brightness, calibration...) live in
//  Settings (lib/settings) and are editable from the knob menu / web UI.
// =============================================================================

// ---------------------------------------------------------------- AS5600 (I2C)
#define PIN_I2C_SDA 21
#define PIN_I2C_SCL 22
#define I2C_FREQ_HZ 400000

// ------------------------------------------------- Rotary encoder (EC11 knob)
#define PIN_KNOB_A  32
#define PIN_KNOB_B  33
#define PIN_KNOB_SW 13
// Quadrature transitions per mechanical detent. Most EC11 knobs are 4, some
// are 2. Run the `test-knob` firmware: it prints raw transitions per detent.
#define KNOB_TRANSITIONS_PER_DETENT 2

// ---------------------------------------------- TMC2209 stepper driver (STEP/DIR)
#define PIN_MOTOR_STEP 27
#define PIN_MOTOR_DIR  14
// WARNING: GPIO12 is a boot strapping pin (flash voltage). If your driver board
// pulls EN high, the ESP32 will not boot. If that happens move EN to GPIO26.
#define PIN_MOTOR_EN   12

// Optional TMC2209 UART (PDN_UART pin). Wire ESP TX -> 1k resistor -> PDN_UART
// and ESP RX -> PDN_UART. If not wired, the firmware falls back to standalone
// mode automatically (microsteps/current set by the driver's pins/pot).
#define PIN_TMC_RX 16
#define PIN_TMC_TX 17
#define TMC_ADDRESS 0        // MS1/MS2 low = address 0
#define TMC_R_SENSE 0.11f    // most TMC2209 modules use 0.11 ohm

// ------------------------------------------------- GC9A01 240x240 round display
#define PIN_TFT_SCLK 18
#define PIN_TFT_MOSI 23
#define PIN_TFT_CS   5
#define PIN_TFT_DC   19
#define PIN_TFT_RST  4
#define PIN_TFT_BL   25
#define TFT_SPI_HZ   40000000

// ----------------------------------------------------------------- Constants
#define DEVICE_NAME       "blinds"          // default hostname -> http://blinds.local
#define WIFI_SETUP_AP     "Blinds-Setup"    // captive portal SSID when no WiFi saved
#define ENCODER_CPR       4096              // AS5600 counts per revolution

#ifndef FW_VERSION
#define FW_VERSION "dev"
#endif

#ifndef SIMULATE_MECHANICS
#define SIMULATE_MECHANICS 0
#endif

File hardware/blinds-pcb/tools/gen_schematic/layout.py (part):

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  53.34, 38.1, '~VIN_JACK', '~VIN_FUSED', 'C18198343')
H('D1', 'Device:D_Schottky', 'SS54', 'Diode_SMD:D_SMA_Handsoldering', 76.2, 38.1, '~VIN_FUSED', '~+12V', 'C7420369', rot=180)
V('D2', 'Device:D_TVS', 'SMBJ15A', 'Diode_SMD:D_SMB_Handsoldering', 88.9, 48.26, '~+12V', 'GND', 'C726824', rot=270)
s.wire('J1.1', 'F1.1'); s.label('VIN_JACK', 35.56, 38.1)
s.wire('F1.2', 'D1.2'); s.label('VIN_FUSED', 58.42, 38.1)
s.wire('D1.1', (104.14, 38.1)); s.power('+12V', 104.14, 38.1); s.flag(96.52, 38.1)
s.wire((88.9, 38.1), 'D2.1')
s.wire('J1.3', (38.1, 40.64), (38.1, 43.18)); s.wire('J1.2', (38.1, 43.18), (38.1, 53.34)); s.power('GND', 38.1, 53.34)
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s.wire('U1.6', 'C4.1'); s.wire('C4.2', (199.39, 38.1))
H('L1', 'Device:L', '4.7uH 3A', 'Inductor_SMD:L_Changjiang_FNR6045S', 208.28, 38.1, '~SW', '~+5V', 'C168067')
s.wire('U1.5', 'L1.1'); s.label('SW', 189.23, 38.1)
s.label('BST', 189.23, 40.64)
s.wire('L1.2', (243.84, 38.1)); s.power('+5V', 243.84, 38.1); s.flag(236.22, 38.1)
for ref, x in (('C5', 220.98), ('C6', 229.87)):
    pass
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R('R4', '22k', 281.94 + X3, 43.18, '~VSENSE', 'GND')
C('C7', '100nF', 294.64 + X3, 43.18, '~VSENSE')
s.wire('R3.2', 'R4.1'); s.wire((281.94 + X3, 36.83), (299.72 + X3, 36.83)); s.wire((294.64 + X3, 36.83), 'C7.1')
s.label('VSENSE', 299.72 + X3, 36.83)
s.text('12 V -> 2.16 V at GPIO36\n(15 V -> 2.70 V)', 300, 60)

# ============ 4. TEST POINTS ============
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    s.wire(f'{rp}.2', (226.06, yrow))
    s.wire(f'{rs}.1', (200.66, yrow)); s.wire((205.74, yrow), f'{c}.1')
    s.label(f'KNOB_{n}', 200.66, yrow, left=True)
s.label('ENC_A', 236.22, 165.1); s.label('ENC_B', 236.22, 180.34)
s.add('SW4', 'Switch:SW_Push', 'TS-1187A', 'Button_Switch_SMD:SW_Push_1P1T_XKB_TS-1187A', 167.64, 172.72, 0,
      {1: ('GND', 5.08), 2: '~KNOB_SW'}, 'C318889')
R('R13', '10k', 180.34, 165.1, '+3V3', '~KNOB_SW'); s.wire('R13.2', (180.34, 172.72))
C('C17', '100nF', 187.96, 177.8, '~KNOB_SW'); s.wire((187.96, 172.72), 'C17.1')
s.wire('SW4.2', (190.5, 172.72)); s.label('KNOB_SW', 190.5, 172.72)

# ============ 9. LCD ============
s.box(270, 142, 340, 204, '9 · LCD  (GC9A01, JST-PH SMD)')
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s.add('Q1', 'Sensor_Optical:TEPT4400', 'TEPT4400 (side-looking)', 'LED_THT:LED_D3.0mm_Horizontal_O1.27mm_Z2.0mm_Clear', 365.76, 165.1, 0,
      {1: '+3V3', 2: '~AMBIENT'}, 'C132178')
R('R14', '4.7k', 368.3, 182.88, '~AMBIENT', 'GND')
s.wire('Q1.2', 'R14.1'); s.wire((368.3, 175.26), (375.92, 175.26)); s.label('AMBIENT', 375.92, 175.26)

# ============ 11. LED RING ============
s.box(12, 208, 296, 279, '11 · LED RING  (10 x WS2812B, 5 V data through level shifter)')
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
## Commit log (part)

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2022-11-09 Edit gitignore
2025-11-09 Create PIO project with ESP32 webtemplate
